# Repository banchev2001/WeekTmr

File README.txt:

Files description:
 ================================================================================
 * DS3231_datasheet.pdf - Data sheet of DS3231 RTCC
 * DS3231_Library_Documentation.pdf - Library documentation by Henning Karlsen
 * RTC_DS3231_LCD_Test.ino - Main source code of the project - using Arduino IDE
 * /libraries/DS3231 contain Henning Karlsen free library with examples
 * /libraries/WeekTimerLibrary/ contain Stoian Banchev library for WeekTimer object
 * /Board/WeekTmr contain cidKad project of the board and schematic 
 
 Board: Arduino nano
 
 Project Conception:
 ================================================================================
 The board have two timers with three layers. Each timer have output. Timer1 
 drives Output-1 (pin 14), Timer2 drives Output-2 (pin 15). Every lyer of timers 
 are connected in "OR" logic to output. Every layer have three settings "On time", "Off time" and 
 Day of week scheme.
 
 Logic Diagram:
 ================================================================================
 
 Timer1, Layer1 ---|
 Timer1, Layer2 ---|-|OR|-Output1 (pin 14)
 Timer1, Layer3 ---|
 
 Timer2, Layer1 ---|
 Timer2, Layer2 ---|-|OR|-Output2 (pin 15)
 Timer2, Layer3 ---|

 Timer settings:
 ==================================================================================
 Days: Days in week in wich timer work,  contain seven fields for every day of week.
 On Time: Hour and minutes of the day that timer start.
 Off Time: Hour and minutes of the day that timer stop.

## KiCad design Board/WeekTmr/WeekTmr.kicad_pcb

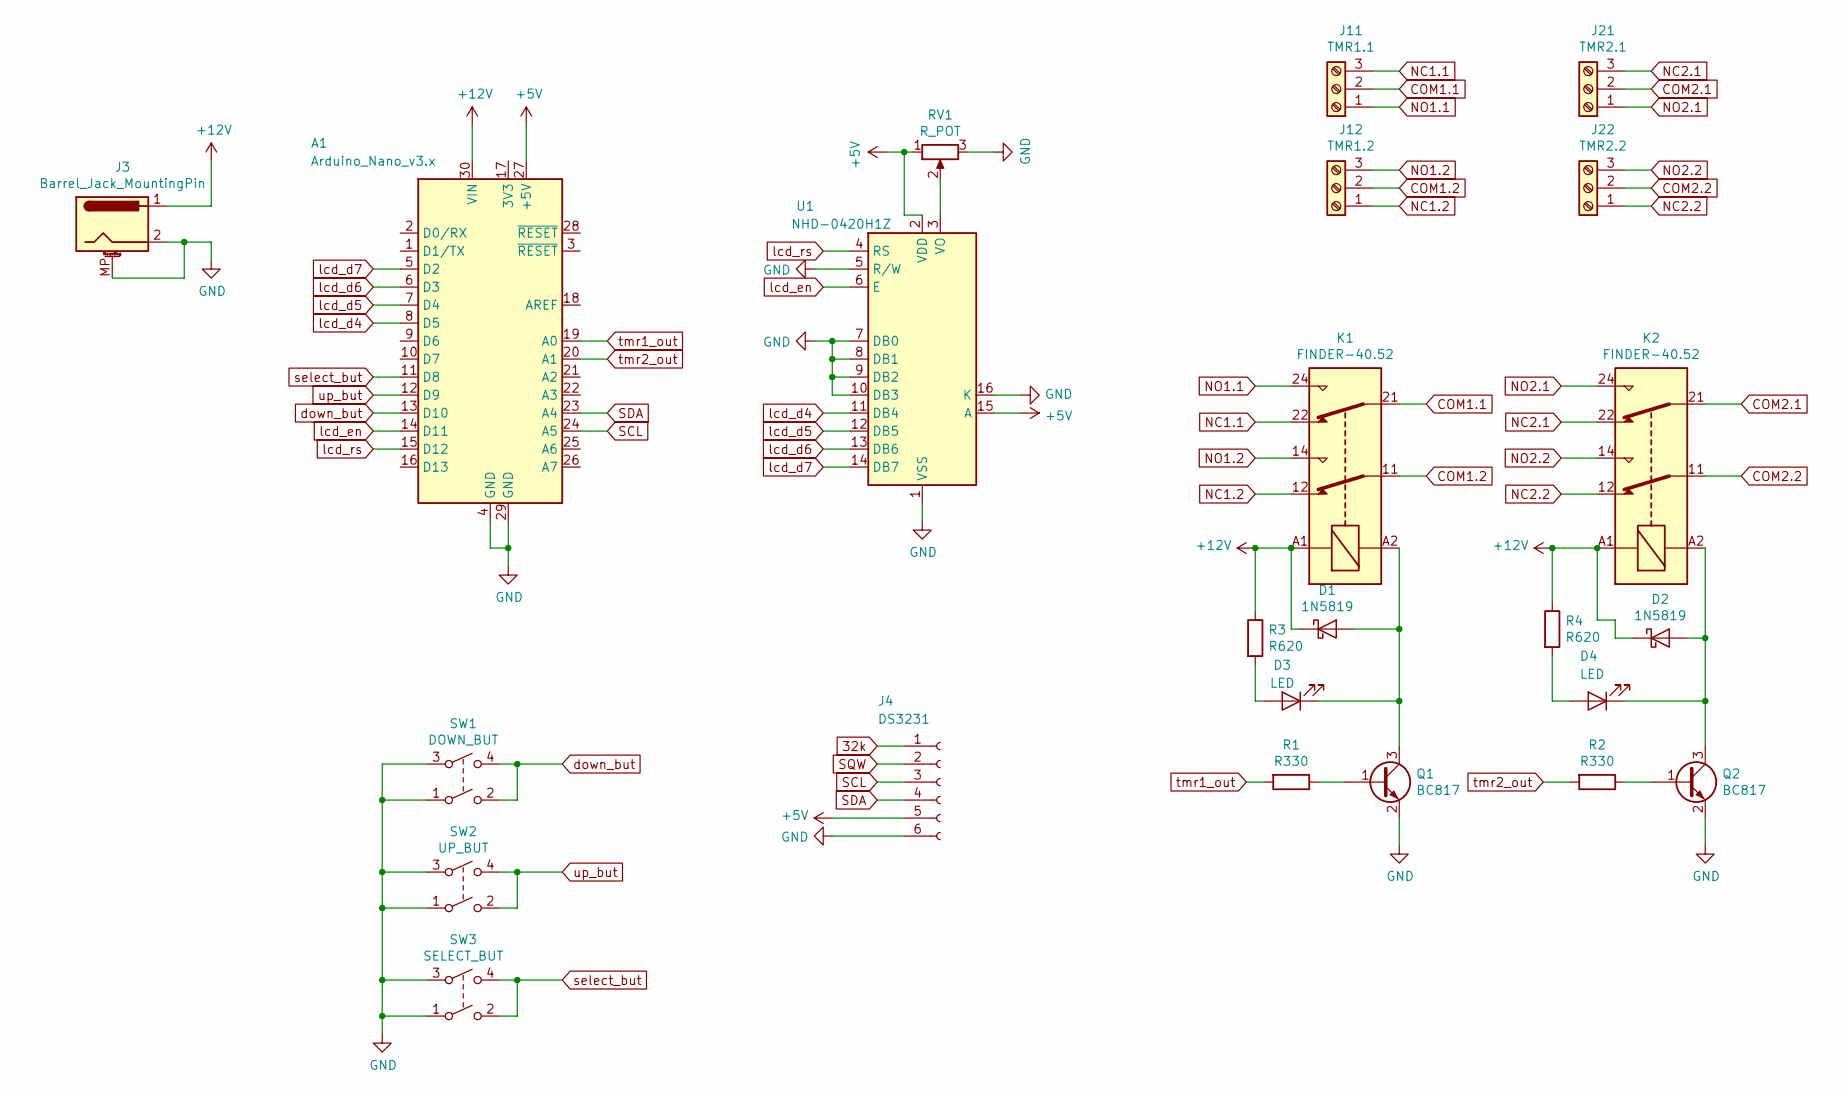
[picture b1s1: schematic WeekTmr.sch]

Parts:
A1: Arduino_Nano_v3.x; Arduino_Nano_direct_Slot
D1, D2: 1N5819; D_DO-41_SOD81_P10.16mm_Horizontal
D3, D4: LED; LED_D5.0mm_Clear
J3: Barrel_Jack_MountingPin; BarrelJack_Horizontal_comet
J4: DS3231; DS3231_RTC_Module
J11: TMR1.1; COMET_2EDGR-5.08-14-00AH
J12: TMR1.2; COMET_2EDGR-5.08-14-00AH
J21: TMR2.1; COMET_2EDGR-5.08-14-00AH
J22: TMR2.2; COMET_2EDGR-5.08-14-00AH
K1, K2: FINDER-40.52; Relay_DPDT_Finder_40.52
Q1, Q2: BC817; SOT-23
R1, R2: R330; R_Axial_DIN0207_L6.3mm_D2.5mm_P15.24mm_Horizontal
R3, R4: R620; R_0805_2012Metric_Pad1.15x1.40mm_HandSolder
RV1: R_POT; Pot_custom
SW1: DOWN_BUT; SW_Button
SW2: UP_BUT; SW_Button
SW3: SELECT_BUT; SW_Button
U1: NHD-0420H1Z; LCD_4x20_Stoian

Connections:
32k: J4.1
+5V: A1.27 (+5V), J4.5, RV1.1, U1.2 (VDD), U1.15 (A)
+12V: A1.30 (VIN), D1.1 (K), D2.1 (K), J3.1, K1.A1, K2.A1, R3.1, R4.1
COM1.1: J11.2, K1.21
COM1.2: J12.2, K1.11
COM2.1: J21.2, K2.21
COM2.2: J22.2, K2.11
GND: A1.4 (GND), A1.29 (GND), J3.2, J3.MP (MountPin), J4.6, Q1.2 (E), Q2.2 (E), RV1.3, SW1.1, SW1.3, SW2.1, SW2.3, SW3.1, SW3.3, U1.1 (VSS), U1.5 (R/W), U1.7 (DB0), U1.8 (DB1), U1.9 (DB2), U1.10 (DB3), U1.16 (K)
NC1.1: J11.3, K1.22
NC1.2: J12.1, K1.12
NC2.1: J21.3, K2.22
NC2.2: J22.1, K2.12
NO1.1: J11.1, K1.24
NO1.2: J12.3, K1.14
NO2.1: J21.1, K2.24
NO2.2: J22.3, K2.14
unnamed: D1.2 (A), D3.1 (K), K1.A2, Q1.3 (C)
unnamed: D2.2 (A), D4.1 (K), K2.A2, Q2.3 (C)
unnamed: D3.2 (A), R3.2
unnamed: D4.2 (A), R4.2
unnamed: Q1.1 (B), R1.1
unnamed: Q2.1 (B), R2.1
unnamed: RV1.2, U1.3 (VO)
SCL: A1.24 (A5), J4.3
SDA: A1.23 (A4), J4.4
SQW: J4.2
down_but: A1.13 (D10), SW1.2, SW1.4
lcd_d4: A1.8 (D5), U1.11 (DB4)
lcd_d5: A1.7 (D4), U1.12 (DB5)
lcd_d6: A1.6 (D3), U1.13 (DB6)
lcd_d7: A1.5 (D2), U1.14 (DB7)
lcd_en: A1.14 (D11), U1.6 (E)
lcd_rs: A1.15 (D12), U1.4 (RS)
select_but: A1.11 (D8), SW3.2, SW3.4
tmr1_out: A1.19 (A0), R1.2
tmr2_out: A1.20 (A1), R2.2
up_but: A1.12 (D9), SW2.2, SW2.4

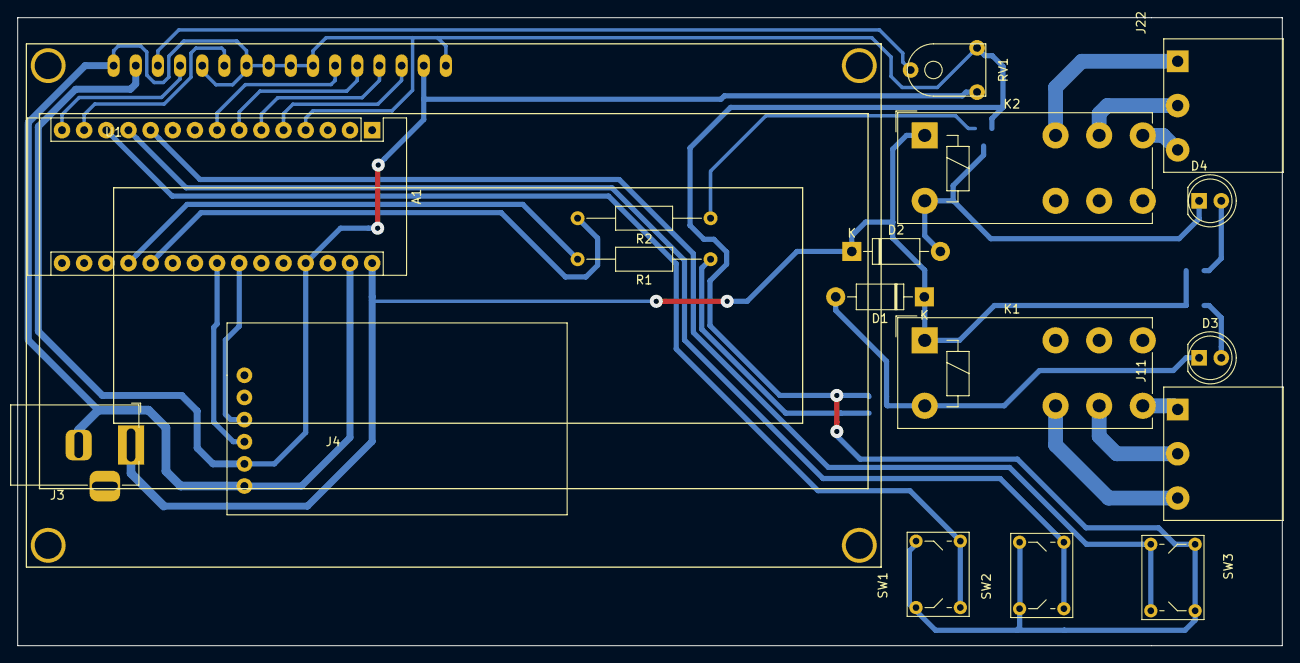
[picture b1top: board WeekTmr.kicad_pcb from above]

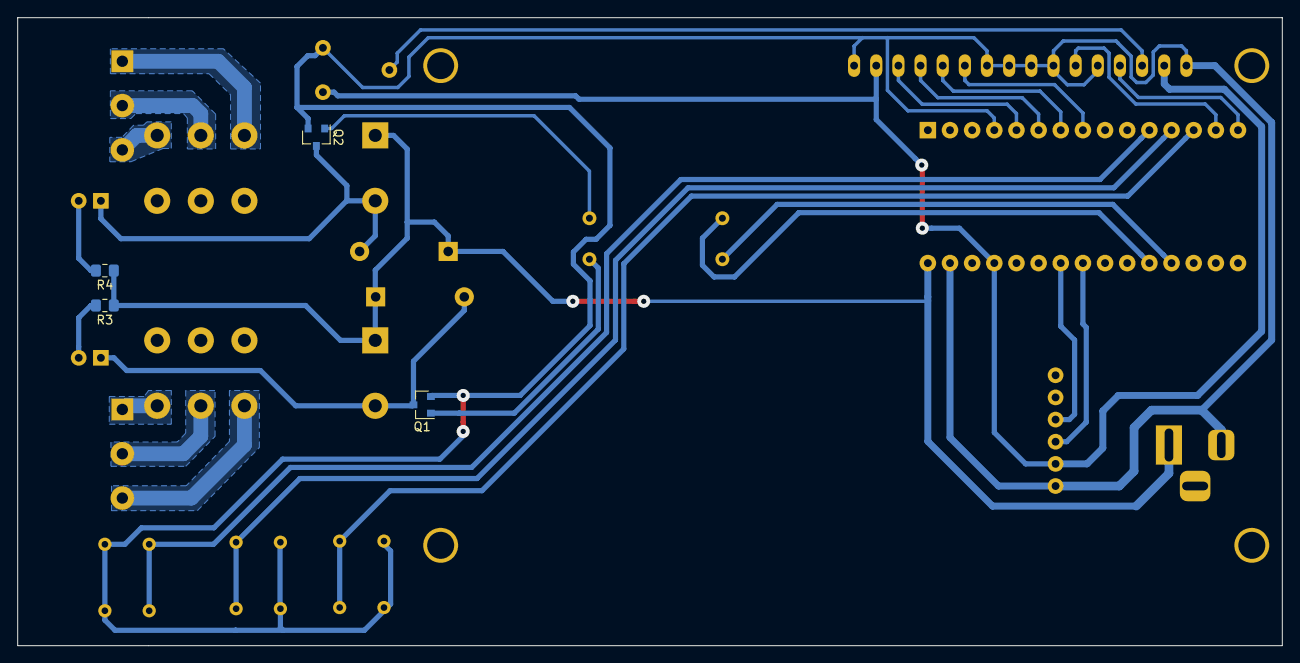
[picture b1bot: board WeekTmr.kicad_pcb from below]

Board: 2 copper layers, 145.0 x 72.0 mm, 22 parts (4 on the bottom side), 29 nets.

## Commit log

2020-10-11 First Official Commit of Week Timer Arduino Project Signed-off-by: banchev2001 <banchev2001@abv.bg>
2020-10-11 Add some extra coments
2020-10-11 Add ReadMe to project
2020-10-11 Add discription
2020-10-11 Description update
2020-10-11 Add start display msg
2020-10-11 VSCode Modify
2020-10-17 Nothing special
2020-10-24 Board update
2020-10-24 update schematic
2020-10-24 pcb update
2020-10-25 schem and board update
2020-12-11 change start display msg
2021-01-02 Add FrancTeh Logo
2021-01-02 New start screen
